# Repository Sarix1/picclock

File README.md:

# PIC Digital Alarm Clock

A digital alarm clock using a PIC16F690 MCU

Created by [Sari Jokinen](https://github.com/sarix1) in December 2023 - February 2024

## Pictures

<table>
  <tr>
    <td></td>
    <td></td>
    <td></td>
  </tr>
  <tr>
    <td></td>
    <td></td>
    <td></td>
  </tr>
  <tr>
    <td></td>
    <td></td>
    <td></td>
  </tr>
  <tr>
    <td></td>
    <td></td>
    <td></td>
  </tr>
</table>

## Components

- PIC16F690 (20-pin, 8-bit MCU)
- 4 x 7-segment LED displays
- 10 x push-buttons
- Rotary encoder with push button
- DHT11 temperature/humidity sensor
- PWM-driven speaker on RC5/P1A
- 4 x SIPO shift registers (CD4094B) for display output
- 2 x PISO shift registers (CD4021B) for button input

## Pinout

### PIC16F690

```
                        _______     _______
                       |       \___/       |
                 +5V --|1 VDD        VSS 20|-- 0V
                       |                   |
              Xtal A ->|2 RA5        RA0 19|-- Unused
                       |   osc1            |
              Xtal B ->|3 RA4        RA1 18|-- Unused
                       |   osc2            |
               Reset ->|4 RA3        RA2 17|-> SIPO Output Enable
                       |   mclr       in   |
PWM / Speaker Signal <~|5 RC5        RC0 16|-> PISO Clock
                       |   p1a        out  |
          SIPO Latch <-|6 RC4        RC1 15|-> PISO Latch
                       |   out        out  |
              Unused --|7 RC3        RC2 14|-- Unused
                       |   p1c        p1d  |
           SIPO Data <-|8 RC6        RB4 13|<-> DHT11
                       |   out        an10 |
          SIPO Clock <-|9 RC7        RB5 12|<- PISO Data
                       |   out        in   |
      Rot. Encoder B ->|10 RB7       RB6 11|<- Rot. Encoder A
                       |    in        in   |
                       '-------------------'
                             PIC16F690
```

### Rotary Encoder
```
       ______    
  A <-|  __  |-> Button: Min/Hour
Gnd --| (__) |
  B <-|______|-- Gnd
```

### Parallel-In, Serial-Out Shift Registers
```
                     ____   ____
     Button Input ->|PI8 \_/ VDD|-- +5V
           Unused <-|Q6      PI7|<- Unused 
        PISO Data <-|Q8      PI6|<- BTN_SENSOR
     BTN_TIME_SET ->|PI4     PI5|<- BTN_SEC_SET
    BTN_ALARM_SET ->|PI3      Q7|-> Unused
      BTN_ENCODER ->|PI2     SER|<- CD4021B 2 Q8 <-.
TN_ALARM_TIMER_ON ->|PI1     CLK|<- PISO Clock     |
               0V --|VSS     LAT|<- PISO Latch     |
                    '-----------'                  |
                      CD4021B 1                    |
.--------------------------------------------------'
|                    ____   ____
|          Unused ->|PI8 \_/ VDD|-- +5V
|          Unused <-|Q6      PI7|<- Unused
'-- CD4021B 1 SER <-|Q8      PI6|<- Unused
       BTN_SNOOZE ->|PI4     PI5|<- Unused
   BTN_BRIGHT_SET ->|PI3      Q7|-> Unused
     BTN_TUNE_SET ->|PI2     SER|-> Unused
   BTN_VOLUME_SET ->|PI1     CLK|<- PISO Clock
               0V --|VSS     LAT|<- PISO Latch
                    '-----------'
                      CD4021B 2
```

### Serial-In, Parallel-Out Shift Registers
```
                     ____   ____
       SIPO Latch ->|LAT \_/ VDD|-- +5V
        SIPO Data ->|DAT      OE|<- LED Enable
       SIPO Clock ->|CLK      Q5|-> 7-Seg 1 E
        7-Seg 1 A <-|Q1       Q6|-> 7-Seg 1 F
        7-Seg 1 B <-|Q2       Q7|-> 7-Seg 1 G
        7-Seg 1 C <-|Q3       Q8|-> Unused
        7-Seg 1 D <-|Q4      Q'S|-> Unused
               0V --|VSS      QS|-> CD4094 2 DAT --.
                    '-----------'                  |
                      CD4094B 1                    |
.--------------------------------------------------'
|                    ____   ____
|      SIPO Latch ->|LAT \_/ VDD|-- +5V
'--> CD4094B 1 QS ->|DAT      OE|<- LED Enable
       SIPO Clock ->|CLK      Q5|-> 7-Seg 2 E
        7-Seg 2 A <-|Q1       Q6|-> 7-Seg 2 F
        7-Seg 2 B <-|Q2       Q7|-> 7-Seg 2 G
        7-Seg 2 C <-|Q3       Q8|-> Unused
        7-Seg 2 D <-|Q4      Q'S|-> Unused
               0V --|VSS      QS|-> CD4094 3 DAT --.
                    '-----------'                  |
                      CD4094B 2                    |
.--------------------------------------------------'
|                    ____   ____
|      SIPO Latch ->|LAT \_/ VDD|-- +5V
'--> CD4094B 2 QS ->|DAT      OE|<- LED Enable
       SIPO Clock ->|CLK      Q5|-> 7-Seg 3 E
        7-Seg 3 A <-|Q1       Q6|-> 7-Seg 3 F
        7-Seg 3 B <-|Q2       Q7|-> 7-Seg 3 G
        7-Seg 3 C <-|Q3       Q8|-> Unused
        7-Seg 3 D <-|Q4      Q'S|-> Unused
               0V --|VSS      QS|-> CD4094 4 DAT --.
                    '-----------'                  |
                      CD4094B 3                    |
.--------------------------------------------------'
|                    ____   ____
|      SIPO Latch ->|LAT \_/ VDD|-- +5V
'--> CD4094B 3 QS ->|DAT      OE|<- LED Enable
       SIPO Clock ->|CLK      Q5|-> 7-Seg 4 E
        7-Seg 4 A <-|Q1       Q6|-> 7-Seg 4 F
        7-Seg 4 B <-|Q2       Q7|-> 7-Seg 4 G
        7-Seg 4 C <-|Q3       Q8|-> Unused
        7-Seg 4 D <-|Q4      Q'S|-> Unused
               0V --|VSS      QS|-> Unused
                    '-----------'                  
                      CD4094B 4
```

## Hardware Layout Overview

```mermaid
graph TD
    subgraph "Buttons"
        BTN[10 Push Buttons]
    end
    
    subgraph "Direct Inputs"
        ENC[Rotary Encoder]
        DHT[DHT11 Sensor]
    end
    
    subgraph "Button Interface"
        PISO2[CD4021B #2]
        PISO1[CD4021B #1]
    end
    
    subgraph "Core"
        PIC[PIC16F690]
    end
    
    subgraph "Display Interface"
        SIPO1[CD4094B #1]
        SIPO2[CD4094B #2]
        SIPO3[CD4094B #3]
        SIPO4[CD4094B #4]
    end
    
    subgraph "Outputs"
        SEG[4x 7-Segment]
        SPK[Speaker]
    end
    
    BTN --> PISO2
    BTN --> PISO1
    PISO2 -->|Serial| PISO1
    PISO1 -->|Pin 12| PIC
    
    ENC -->|Pins 10,11| PIC
    DHT <-->|Pin 13| PIC
    
    PIC -->|Pin 8| SIPO1
    SIPO1 --> SIPO2
    SIPO2 --> SIPO3
    SIPO3 --> SIPO4
    
    SIPO1 --> SEG
    SIPO2 --> SEG
    SIPO3 --> SEG
    SIPO4 --> SEG
    
    PIC -->|Pin 5| SPK
```

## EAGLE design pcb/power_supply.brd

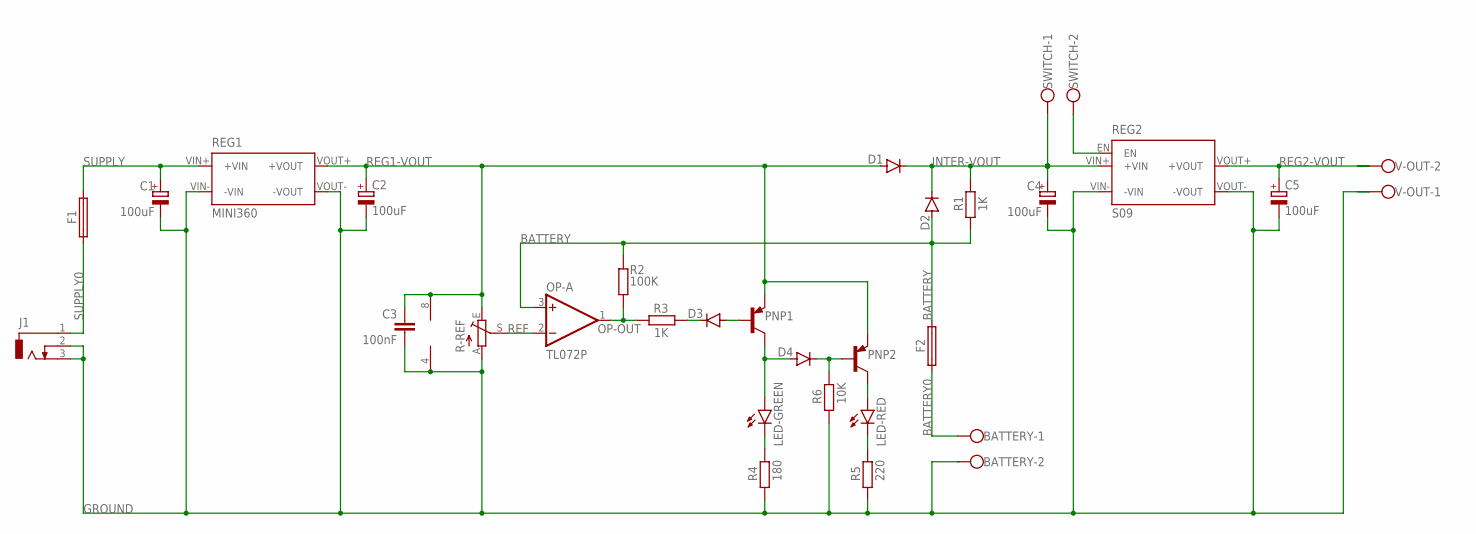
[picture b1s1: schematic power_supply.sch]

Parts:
BATTERY: W237-102
C1, C2: 100uF; E5-6
C3: 100nF; C5B2.5
C4, C5: 100uF; E2-5
D1, D2, D3, D4: BAS15; DO34-7
F1, F2: SH22,5
J1: DCJ0303
LED-GREEN: LED5MM
LED-RED: LED5MM
OP-: TL072P; DIL08
PNP1, PNP2: BC557A-PNP-TO92-EBC; TO92-EBC
R1, R3: 1K; 0204/7
R2: 100K; 0204/7
R4: 180; 0204/7
R5: 220; 0204/7
R6: 10K; 0204/7
R-REF: TRIM_EU-PT10; PT-10
REG1: MINI360; DC-DC-CONVERTER-MINI360
REG2: S09; DC-DC-CONVERTER-S09
SWITCH: W237-102
V-OUT: W237-102

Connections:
BATTERY: D2.A, F2.1, OP-.3 (+IN), R1.1, R2.2
BATTERY0: BATTERY.1, F2.2
ENABLE: REG2.EN, SWITCH.2
GROUND: BATTERY.2, C1.-, C2.-, C3.2, C4.-, C5.-, J1.2, J1.3, OP-.4 (V-), R4.1, R5.1, R6.1, R-REF.A, REG1.VIN- (-VIN), REG1.VOUT- (-VOUT), REG2.VIN- (-VIN), REG2.VOUT- (-VOUT), V-OUT.1
INTER-VOUT: C4.+, D1.C, D2.C, R1.2, REG2.VIN+ (+VIN), SWITCH.1
unnamed: LED-RED.A, PNP2.C
unnamed: D3.C, R3.1
unnamed: D3.A, PNP1.B
unnamed: D4.A, LED-GREEN.A, PNP1.C
unnamed: D4.C, PNP2.B, R6.2
unnamed: LED-RED.K (C), R5.2
unnamed: LED-GREEN.K (C), R4.2
OP-OUT: OP-.1 (OUT), R2.1, R3.2
REF: OP-.2 (-IN), R-REF.S
REG1-VOUT: C2.+, C3.1, D1.A, OP-.8 (V+), PNP1.E, PNP2.E, R-REF.E, REG1.VOUT+ (+VOUT)
REG2-VOUT: C5.+, REG2.VOUT+ (+VOUT), V-OUT.2
SUPPLY: C1.+, F1.2, REG1.VIN+ (+VIN)
SUPPLY0: F1.1, J1.1

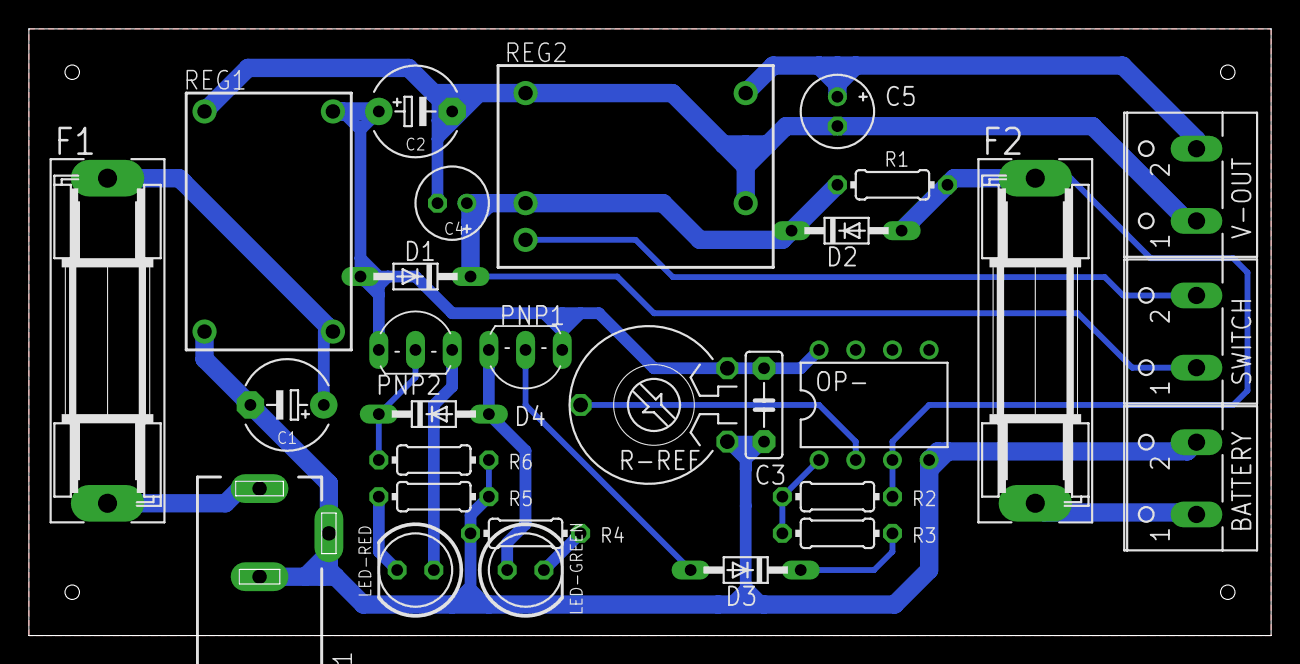
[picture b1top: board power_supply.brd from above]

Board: 2 copper layers, 86.0 x 42.0 mm, 29 parts (0 on the bottom side), 18 nets.

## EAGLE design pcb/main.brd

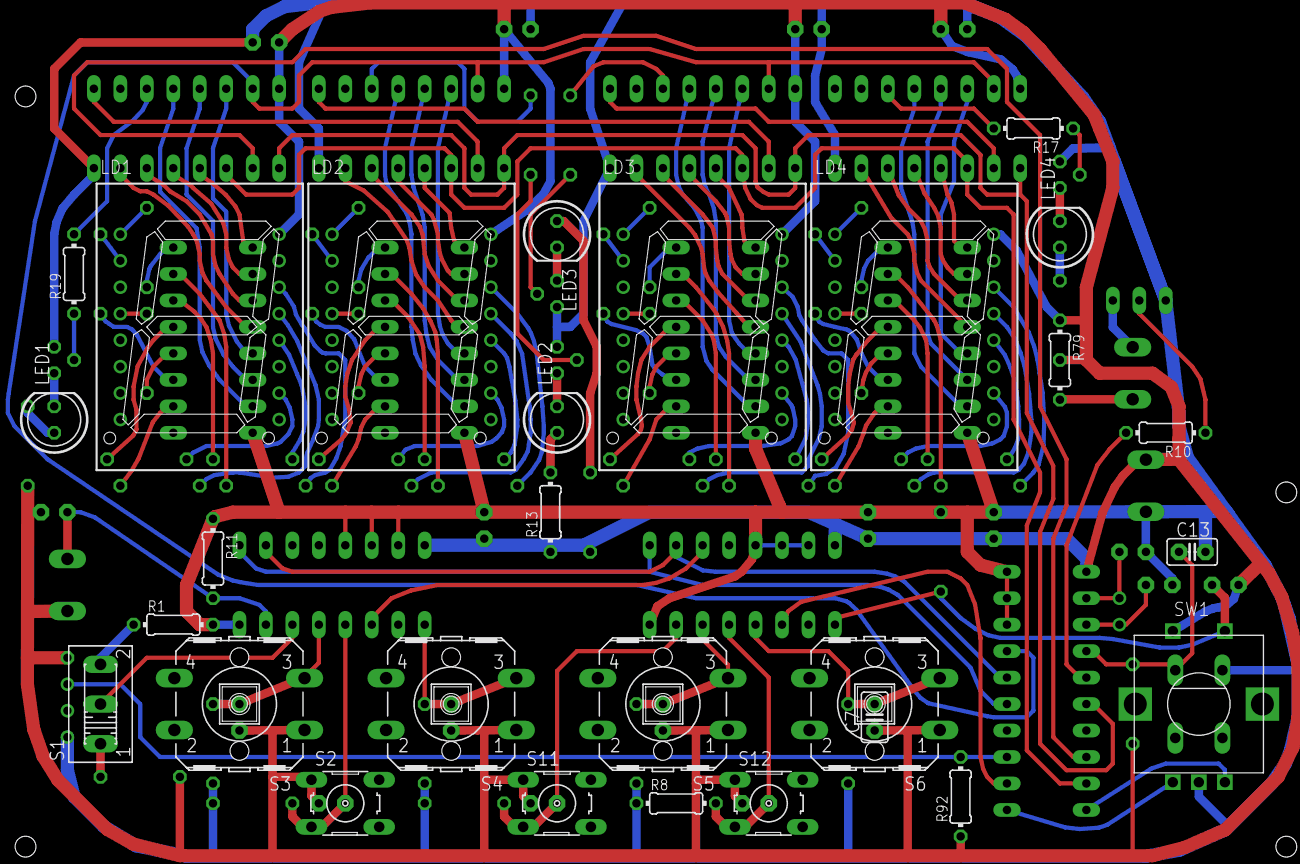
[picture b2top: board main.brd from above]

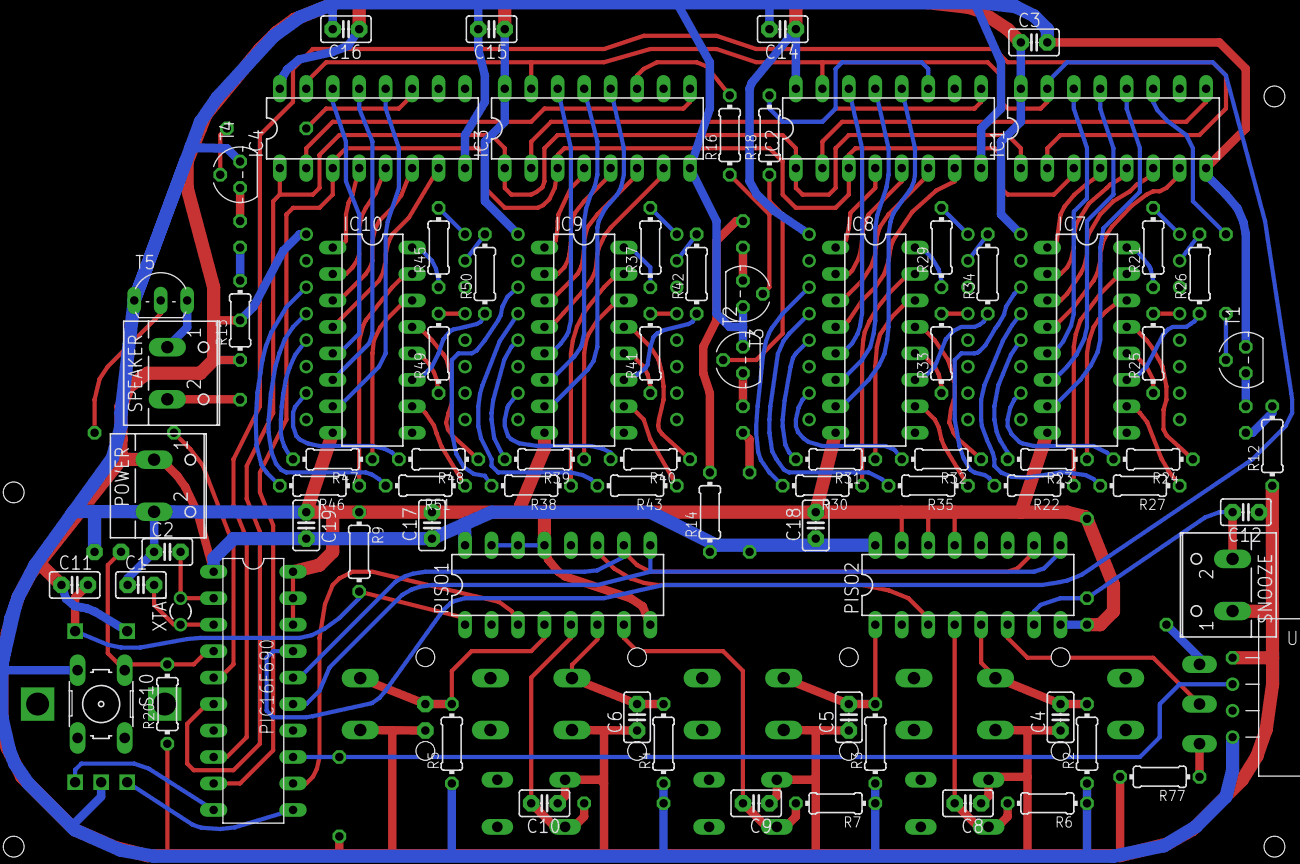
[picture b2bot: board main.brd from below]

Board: 2 copper layers, 109 parts (81 on the bottom side), 135 nets.

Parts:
C1, C2: 10pF; C2.5-2
C3, C14, C15, C16, C17, C18, C19: 100nF; C2.5-2
C4, C5, C6, C7, C8, C9, C10, C11, C12, C13: 68nF; C2.5-2
IC1, IC2, IC3, IC4: 4094N; DIL16
IC7, IC8, IC9, IC10: ULN2003AN; DIL16
LD1, LD2, LD3, LD4: SA08-11; SA08
LED1, LED2, LED3, LED4: LED5MM
PIC16F690: DIL20
PISO1, PISO2: 4021N; DIL16
POWER: W237-102
R1, R2, R3, R4, R5, R6, R7, R8, R9, R11, R20, R77: 560; 0204/7
R10, R16, R17, R18, R19: 1K; 0204/7
R12, R13, R14, R15, R21, R22, R23, R24, R25, R26, R27, R29, R30, R31, R32, R33, R34, R35, R37, R38, R39, R40, R41, R42, R43, R45, R46, R47, R48, R49, R50, R51: 200; 0204/7
R79: 100; 0204/7
R92: 5K; 0204/7
S1: 255SB
S2, S10, S11, S12: B3F-10XX
S3, S4, S5, S6: B3F-40XX
SNOOZE: W237-102
SPEAKER: W237-102
SW1: EC12E_SW; ALPS_EC12E_SW
T1, T2, T3, T4: BC547; TO92
T5: TO92-EBC
U1: RHT03_DHT-22/RA
XTAL: TC26V

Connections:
BTN_ALARM_SET: C4.2, PISO2.5, R2.2, S3.3
BTN_ALARM_TIMER_ON: PISO2.6, S1.2
BTN_BRIGHT_SET: C10.2, PISO1.5, R8.2, S12.3
BTN_ENCODER: C11.2, PISO1.1, R9.2, SW1.E
BTN_RESET: C13.1, PIC16F690.4, R20.2, S10.1
BTN_SEC_SET: C6.2, PISO1.6, R4.2, S5.3
BTN_SENSOR: C7.2, PISO1.4, R5.2, S6.3
BTN_SNOOZE: C12.2, PISO2.7, R11.2, SNOOZE.2
BTN_TIME_SET: C5.2, PISO2.1, R3.2, S4.3
BTN_TUNE_SET: C9.2, PISO1.7, R7.2, S11.3
BTN_VOLUME_SET: C8.2, PISO2.4, R6.2, S2.3
DHT11: PIC16F690.13, R92.2, U1.DATA
ENC_A: PIC16F690.11, SW1.A
ENC_B: PIC16F690.10, SW1.B
unnamed: C1.2, PIC16F690.3, XTAL.1
unnamed: C2.2, PIC16F690.2, XTAL.2
unnamed: IC7.16, R21.1
unnamed: IC7.15, R22.1
unnamed: IC7.14, R23.1
unnamed: R10.1, T5.B
unnamed: R18.1, T2.2
unnamed: IC3.4, IC9.1
unnamed: IC3.5, IC9.2
unnamed: IC3.6, IC9.3
unnamed: IC3.7, IC9.4
unnamed: IC3.14, IC9.5
unnamed: IC3.13, IC9.6
unnamed: IC3.12, IC9.7
unnamed: IC1.11, R19.2
unnamed: IC2.4, IC8.1
unnamed: IC2.5, IC8.2
unnamed: IC7.13, R24.1
unnamed: IC7.12, R25.1
unnamed: IC7.11, R26.1
unnamed: IC2.6, IC8.3
unnamed: IC2.7, IC8.4
unnamed: IC2.14, IC8.5
unnamed: IC2.13, IC8.6
unnamed: IC2.12, IC8.7
unnamed: IC2.11, R18.2
unnamed: IC1.4, IC7.1
unnamed: IC1.5, IC7.2
unnamed: IC1.6, IC7.3
unnamed: IC1.7, IC7.4
unnamed: IC1.14, IC7.5
unnamed: IC1.13, IC7.6
unnamed: IC1.12, IC7.7
unnamed: IC3.11, R16.2
unnamed: IC4.4, IC10.1
unnamed: IC4.5, IC10.2
unnamed: IC4.6, IC10.3
unnamed: IC4.7, IC10.4
unnamed: IC4.14, IC10.5
unnamed: IC4.13, IC10.6
unnamed: IC4.12, IC10.7
unnamed: IC4.11, R17.2
unnamed: LD1.1, R21.2
unnamed: LD1.14, R22.2
unnamed: LD1.12, R23.2
unnamed: LD1.10, R24.2
unnamed: LD1.4, R25.2
unnamed: LD1.2, R26.2
unnamed: LD1.13, R27.2
unnamed: LD2.1, R29.2
unnamed: LD2.14, R30.2
unnamed: LD2.12, R31.2
unnamed: LD2.10, R32.2
unnamed: LD2.4, R33.2
unnamed: LD2.2, R34.2
unnamed: LD2.13, R35.2
unnamed: LD3.1, R37.2
unnamed: LD3.14, R38.2
unnamed: LD3.12, R39.2
unnamed: LD3.10, R40.2
unnamed: LD3.4, R41.2
unnamed: LD3.2, R42.2
unnamed: LD3.13, R43.2
unnamed: LD4.1, R45.2
unnamed: LD4.14, R46.2
unnamed: LD4.12, R47.2
unnamed: LD4.10, R48.2
unnamed: LD4.4, R49.2
unnamed: LD4.2, R50.2
unnamed: LD4.13, R51.2
unnamed: LED1.K, T1.3
unnamed: LED2.K, T2.3
unnamed: LED3.K, T3.3
unnamed: LED4.K, T4.3
unnamed: R19.1, T1.2
unnamed: R16.1, T3.2
unnamed: R17.1, T4.2
unnamed: LED4.A, R15.2
unnamed: LED3.A, R14.2
unnamed: LED2.A, R13.2
unnamed: LED1.A, R12.2
unnamed: IC7.10, R27.1
unnamed: IC1.9, IC2.2
unnamed: IC2.9, IC3.2
unnamed: IC3.9, IC4.2
unnamed: IC8.16, R29.1
unnamed: IC8.15, R30.1
unnamed: IC8.14, R31.1
unnamed: IC8.13, R32.1
unnamed: IC8.12, R33.1
unnamed: IC8.11, R34.1
unnamed: IC8.10, R35.1
unnamed: IC9.16, R37.1
unnamed: IC9.15, R38.1
unnamed: IC9.14, R39.1
unnamed: IC9.13, R40.1
unnamed: IC9.12, R41.1
unnamed: IC9.11, R42.1
unnamed: IC9.10, R43.1
unnamed: IC10.16, R45.1
unnamed: IC10.15, R46.1
unnamed: IC10.14, R47.1
unnamed: IC10.13, R48.1
unnamed: IC10.12, R49.1
unnamed: IC10.11, R50.1
unnamed: IC10.10, R51.1
unnamed: R77.1, S1.1
unnamed: R1.1, S1.3
unnamed: R79.2, SPEAKER.2
unnamed: SPEAKER.1, T5.C
PISO-CONNECT: PISO1.11, PISO2.3
PISO_CLK: PIC16F690.16, PISO1.10, PISO2.10
PISO_DAT: PIC16F690.12, PISO1.3
PISO_LAT: PIC16F690.15, PISO1.9, PISO2.9
PWM: PIC16F690.5, R10.2
SIPO_CLK: IC1.3, IC2.3, IC3.3, IC4.3, PIC16F690.9
SIPO_DAT: IC1.2, PIC16F690.8
SIPO_LAT: IC1.1, IC2.1, IC3.1, IC4.1, PIC16F690.6
SIPO_OE: IC1.15, IC2.15, IC3.15, IC4.15, PIC16F690.17
VDD: C3.1, C4.1, C5.1, C6.1, C7.1, C8.1, C9.1, C10.1, C11.1, C12.1, C14.1, C15.1, C16.1, C17.1, C18.1, C19.2, IC1.16, IC2.16, IC3.16, IC4.16, LD1.16, LD2.16, LD3.16, LD4.16, PIC16F690.1, PISO1.16, PISO2.16, POWER.1, R12.1, R13.1, R14.1, R15.1, R20.1, R77.2, R79.1, R92.1, S2.1, S3.1, S4.1, S5.1, S6.1, S11.1, S12.1, SNOOZE.1, SW1.D, U1.VDD
VSS: C1.1, C2.1, C3.2, C13.2, C14.2, C15.2, C16.2, C17.2, C18.2, C19.1, IC1.8, IC2.8, IC3.8, IC4.8, IC7.8, IC8.8, IC9.8, IC10.8, PIC16F690.18, PIC16F690.19, PIC16F690.20, PISO1.8, PISO1.13, PISO1.14, PISO1.15, PISO2.8, PISO2.13, PISO2.14, PISO2.15, POWER.2, R1.2, R2.1, R3.1, R4.1, R5.1, R6.1, R7.1, R8.1, R9.1, R11.1, S10.3, SW1.C, T1.1, T2.1, T3.1, T4.1, T5.E, U1.GND

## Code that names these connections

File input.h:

#ifndef INPUT_H
#define INPUT_H

// All buttons are active high, with pull-down resistors to hold them low
// Push = When hit once, triggers a function at a rising edge signal
// Hold = When held down, selects and displays a specific program state
// Switch = Sets program options depending on logic high or low
// Virtual buttons are used for input events generated by the code
enum BUTTON_BIT
{
    // PISO 1
    BTN_ALARM_TIMER_ON = 0, // PI1 (Switch)
    BTN_ENCODER     = 1,  // PI2 (Push)
    BTN_ALARM_SET   = 2,  // PI3 (Hold/Push)
    BTN_TIME_SET    = 3,  // PI4 (Hold)
    BTN_SEC_SET     = 4,  // PI5 (Hold)
    BTN_SENSOR      = 5,  // PI6 (Hold)
    
    // PISO 2
    BTN_VOLUME_SET  = 8,  // PI1 (Hold)
    BTN_TUNE_SET    = 9,  // PI2 (Hold)
    BTN_BRIGHT_SET  = 10, // PI3 (Hold)
    BTN_SNOOZE      = 11, // PI4 (Hold/Push)
    
    // virtual buttons
    BTN_ENCODER_CW  = 13,
    BTN_ENCODER_CCW = 14,
    BTN_NONE        = 15
};

// Buttons that cannot be pushed simultaneously
#define BTN_HOLD_MASK ( \
    (1<<BTN_ALARM_SET)  | \
    (1<<BTN_TIME_SET)   | \
    (1<<BTN_SEC_SET)    | \
    (1<<BTN_SENSOR)     | \
    (1<<BTN_VOLUME_SET) | \
    (1<<BTN_SNOOZE))

    //(1<<BTN_TUNE_SET)   | \
    //(1<<BTN_BRIGHT_SET) | \

#define ENCODER_CCW 0
#define ENCODER_CW  1
#define ENC_MAX_EVENTS 15

#endif/* INPUT_H */

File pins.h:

#ifndef PINS_H
#define	PINS_H

#include "macro.h"

#define AUDIO_PIN    PWM_A // pin 5
#define DHT11_PIN    B,4 // pin 13
#define SIPO_OE      A,2 // pin 17

#define SIPO_LAT_PIN C,4 // pin 6
#define SIPO_CLK_PIN C,7 // pin 9
#define SIPO_DAT_PIN C,6 // pin 8

#define PISO_LAT_PIN C,1 // pin 15
#define PISO_CLK_PIN C,0 // pin 16
#define PISO_DAT_PIN B,5 // pin 12

#define ENC_PIN_A    B,6 // pin 11
#define ENC_PIN_B    B,7 // pin 10
#define ENC_PIN_BOTH (PORT_NTH_BIT(ENC_PIN_A) | PORT_NTH_BIT(ENC_PIN_B))

#endif	/* PINS_H */

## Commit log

2024-02-14 Refactoring
2025-06-17 move code files to src/ and images to img/
2025-06-17 Fix wrong link to image
